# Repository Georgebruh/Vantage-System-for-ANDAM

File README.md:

# Vantage

Design files and firmware of the **Vantage** IoT sensor node, by Team sevenUP. The node is the field unit of a
flood-monitoring system. This repository holds the hardware (schematics, PCB layout, libraries, drawings and the
instruction documents) and the node firmware.

**Current release: Rev B** (2026-11-05), tag `rev-B`: power board Rev B, sensor board Rev A (unchanged).

| Board | Status |
|---|---|
| Sensor board | Schematic and PCB complete. Single-sided, made at home by toner transfer. |
| Power board | Schematic and PCB complete. One copper layer, made at home by toner transfer, same outline and mounting holes as the sensor board. |

The node is two boards joined by one 6-way JST XH cable (J1 to J1):

- **Sensor board**: carries the ESP32-S3 dev board (YD-ESP32-S3, header rows 25.4 mm apart) and the sensor
  interfaces: AJ-SR04M ultrasonic, BME280, rain gauge, TF-Luna (optional).
- **Power board**: protected 1S battery pack, solar MPPT charger module, 3.3 V LDO with ideal diode, switched
  5 V boost for the sensors (SENS_EN) and two INA226 current monitor modules.

## Repository layout

```
Vantage-Hardware/
├── sensor-board/           KiCad project of the sensor board (schematic + PCB)
├── power-board/            KiCad project of the power board (schematic + PCB)
├── lib/                    shared Vantage symbol and footprint library
├── outputs/
│   ├── sensor-board/       schematic PDF, copper artwork, assembly drawing, BOM, drill table
│   └── power-board/        schematic PDF, copper artwork, assembly drawing, envelope, BOM, drill table
├── docs/                   instruction documents (PDF)
│   └── src/                document sources, figures, fonts and build script
├── firmware/               ESP32-S3 firmware (PlatformIO) and the gateway receiver
└── tools/                  script that regenerates the drawings in outputs/
```

## Files

### KiCad design files

| File | Description |
|---|---|
| `sensor-board/Vantage_Sensor.kicad_pro` | Sensor board project (design rules for toner transfer: 0.6 / 1.0 mm tracks, 0.5 mm gaps) |
| `sensor-board/Vantage_Sensor.kicad_sch` | Sensor board schematic |
| `sensor-board/Vantage_Sensor.kicad_pcb` | Sensor board PCB, 110 × 30 mm, copper on the bottom only, two wire links on top |
| `sensor-board/fp-lib-table`, `sym-lib-table` | Project library tables, pointing to `lib/` |
| `power-board/Vantage_Power.kicad_pro` | Power board project (same design rules for toner transfer as the sensor board) |
| `power-board/Vantage_Power.kicad_sch` | Power board schematic |
| `power-board/Vantage_Power.kicad_pcb` | Power board PCB, 110 × 30 mm, copper on the bottom only, two wire links on top |
| `power-board/Vantage_Power.kicad_dru` | Custom design rule: 0.35 mm clearance between the pins of the SOT-23 parts |
| `power-board/fp-lib-table`, `sym-lib-table` | Project library tables, pointing to `lib/` |

### Library

| File | Description |
|---|---|
| `lib/Vantage.kicad_sym` | Symbols: ESP32-S3 dev board, INA226 module, CN3791 module, MAX40200, MT3608, RT9080-33, TPS2051B |
| `lib/Vantage.pretty/` | Footprints with enlarged pads for toner transfer and hand drilling; SMD footprints placed on the copper side |

### Drawings and tables (`outputs/`)

| File | Description |
|---|---|
| `outputs/sensor-board/Vantage_Sensor_Schematic.pdf` | Sensor board schematic |
| `outputs/sensor-board/Vantage_Sensor_Copper-Artwork_Letter.pdf` | Copper artwork, 1:1, four copies on US Letter. **Print at 100 % / Actual size, do not mirror.** |
| `outputs/sensor-board/Vantage_Sensor_Copper-Artwork_A4.pdf` | Same, on A4 |
| `outputs/sensor-board/Vantage_Sensor_Assembly-Drawing.pdf` | Assembly drawing, 2:1: component side and copper side |
| `outputs/sensor-board/Vantage_Sensor_BOM.csv` | Sensor board bill of materials |
| `outputs/sensor-board/Vantage_Sensor_Drill.csv` | Drill sizes and counts |
| `outputs/power-board/Vantage_Power_Schematic.pdf` | Power board schematic |
| `outputs/power-board/Vantage_Power_Copper-Artwork_Letter.pdf` | Copper artwork, 1:1, four copies on US Letter. **Print at 100 % / Actual size, do not mirror.** |
| `outputs/power-board/Vantage_Power_Copper-Artwork_A4.pdf` | Same, on A4 |
| `outputs/power-board/Vantage_Power_Assembly-Drawing.pdf` | Assembly drawing, 2:1: component side and copper side |
| `outputs/power-board/Vantage_Power_Envelope.pdf` | Module envelope, 1:1: the space the assembled board needs in the enclosure |
| `outputs/power-board/Vantage_Power_BOM.csv` | Power board bill of materials |
| `outputs/power-board/Vantage_Power_Drill.csv` | Drill sizes and counts |

### Documents (`docs/`)

The documents follow the layout of ISO documents: cover, contents, foreword, introduction, numbered clauses
(scope, references, terms, ...), normative and informative annexes, bibliography.

| File | Description |
|---|---|
| `docs/VNT-001_Sensor-board_Fabrication-assembly-test.pdf` | **VNT-001** Vantage — Sensor board — Fabrication, assembly and test |
| `docs/VNT-002_Power-board_Fabrication-assembly-test.pdf` | **VNT-002** Vantage — Power board — Fabrication, assembly and test |
| `docs/src/VNT-001.md`, `VNT-002.md` | Document sources (edit these, then rebuild the PDFs) |
| `docs/src/build.py` | Builds the PDFs from the sources |
| `docs/src/iso.css` | Page layout and styles |
| `docs/src/figures/` | Figures used by the documents |
| `docs/src/fonts/` | Caladea font (SIL Open Font License, `OFL.txt`) |

### Firmware (`firmware/`)

| File | Description |
|---|---|
| `firmware/README.md` | Setup, build environments, power modes and the data format |
| `firmware/platformio.ini` | PlatformIO project: `field` (normal operation) and `bench` (bench and functional tests) |
| `firmware/include/config.h` | Node ID, gateway URL, mounting height, intervals and battery thresholds |
| `firmware/include/pins.h` | Pin map (VNT-001, Annex C) |
| `firmware/include/secrets.example.h` | Template for the Wi-Fi credentials; copy to `secrets.h`, which is not committed |
| `firmware/src/` | Firmware sources: sensors, rain gauge, power monitors, uplink, sleep and power modes |
| `firmware/tools/receiver.py` | Receiver for the gateway computer; writes the readings to a CSV file |

### Tools

| File | Description |
|---|---|
| `tools/make_outputs.py` | Regenerates the schematic PDFs, copper artwork, assembly drawings, power board envelope and document figures with `kicad-cli`; `python3 tools/make_outputs.py power` does one board |

## Opening the design

The KiCad files are in the KiCad 7 format; KiCad 8, 9 and 10 open them. The first save in KiCad 10 upgrades the
file format; commit that upgrade on its own, without other changes, so later diffs stay readable.

Both projects use the shared library in `lib/` through their own library tables, so no global library setup is
needed.

## Title blocks

Every file carries the same title block content: **Team sevenUP**, title **Vantage — Sensor board** or
**Vantage — Power board**, date and revision. No comment lines. The documents carry the same fields in the title
block on their cover.

## Revisions

All files of a release share one revision letter, shown in every title block and on the document covers. Each
release is tagged `rev-<letter>` and listed in [`CHANGELOG.md`](CHANGELOG.md). Things that need to change are
tracked as GitHub issues.

To make a new revision:

1. Change the design in KiCad.
2. Set the new revision letter and date in the title block of every changed file (Page Settings in KiCad).
3. Regenerate the drawings: `python3 tools/make_outputs.py`, or plot them from KiCad.
4. Update the BOM and drill CSV files if parts or holes changed.
5. Update the document sources (`edition`, `date`, `rev` and the content) and rebuild: `python3 docs/src/build.py`.
6. Add the revision to `CHANGELOG.md`, commit, and tag it `rev-<letter>`.

## Rebuilding the outputs

Drawings (needs KiCad's `kicad-cli` on the PATH, or its path in `KICAD_CLI`):

```
pip install pypdf reportlab
python3 tools/make_outputs.py
```

Documents:

```
pip install markdown beautifulsoup4 weasyprint
python3 docs/src/build.py
```

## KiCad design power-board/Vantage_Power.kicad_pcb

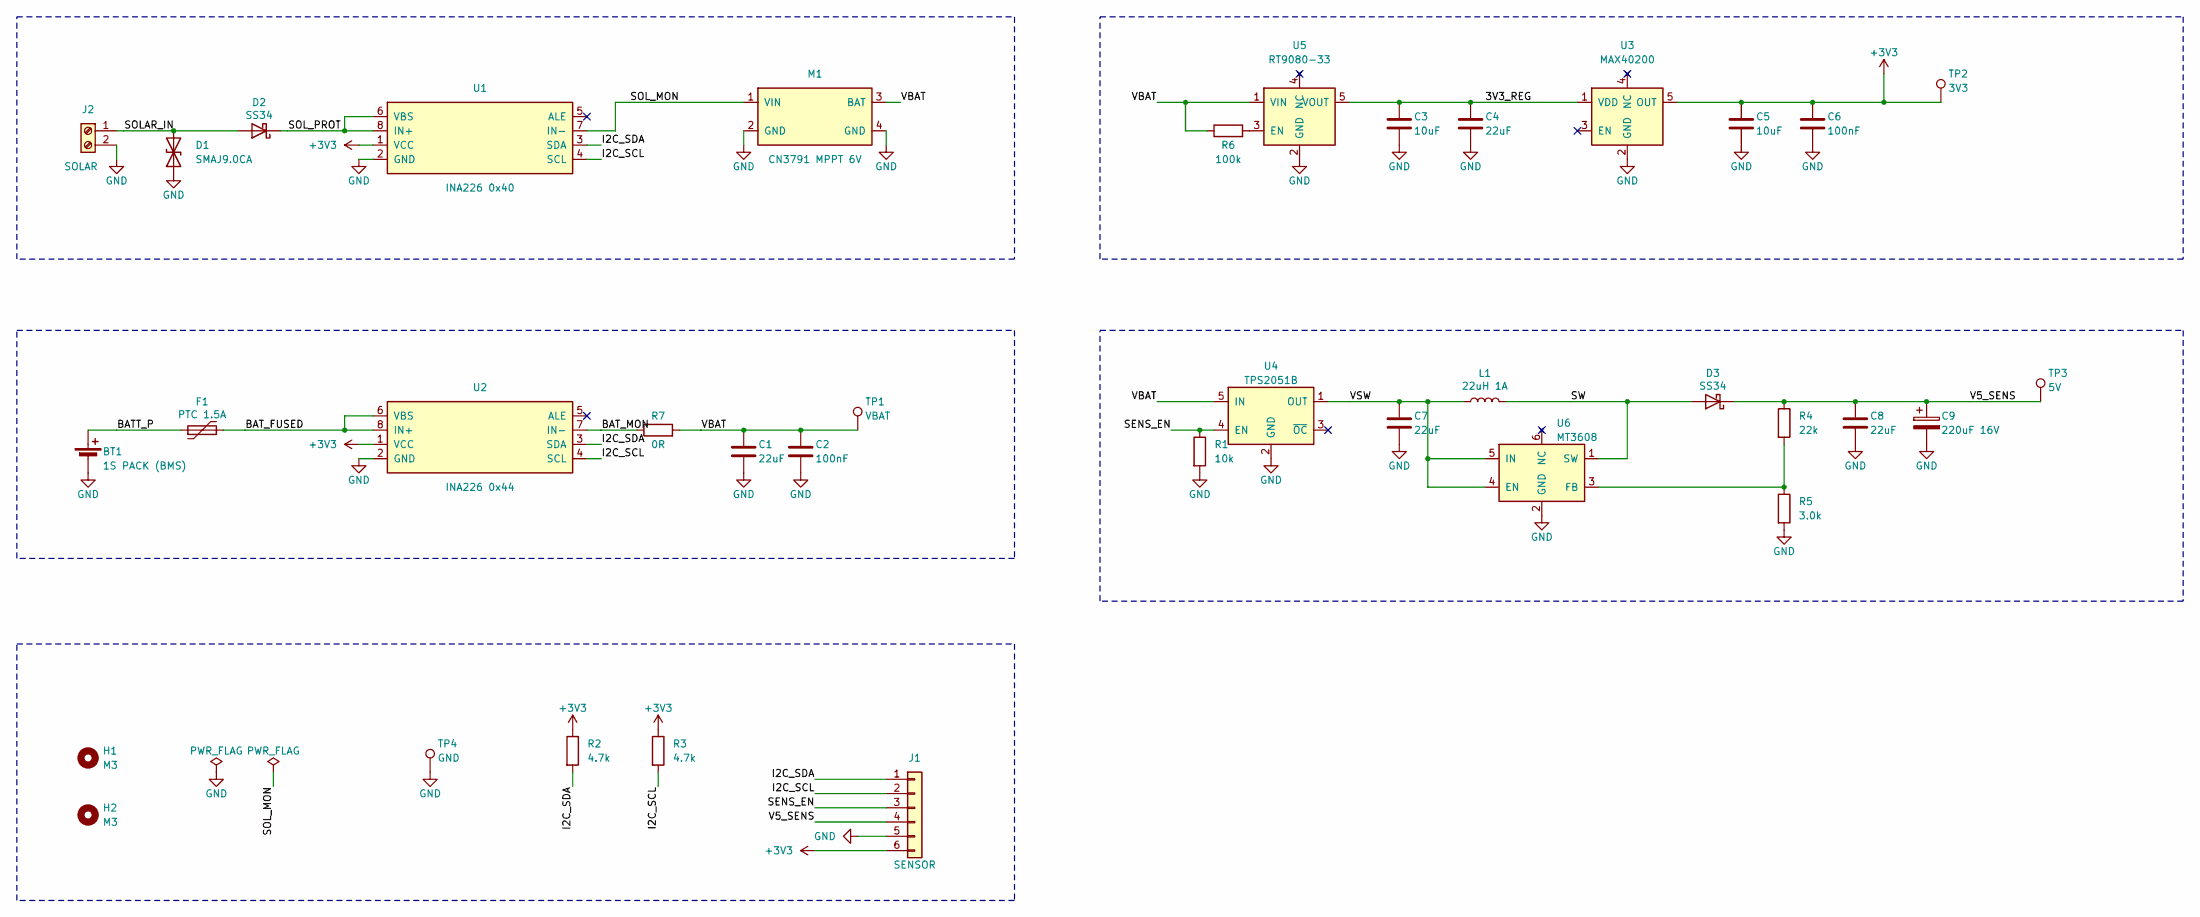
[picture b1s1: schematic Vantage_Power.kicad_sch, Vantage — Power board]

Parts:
BT1: 1S PACK (BMS); JST_XH_S2B-XH-A_1x02_P2.50mm_Horizontal_Toner
C1, C4, C7, C8: 22uF; C_1206_HandSolder_Bottom
C2, C6: 100nF; C_1206_HandSolder_Bottom
C3, C5: 10uF; C_1206_HandSolder_Bottom
C9: 220uF 16V; CP_Radial_D6.3mm_P2.50mm_Toner
D1: SMAJ9.0CA; D_SMA_HandSolder_Bottom_WideGap
D2: SS34; D_SMA_HandSolder_Bottom_WideGap
D3: SS34; D_SMA_HandSolder_Bottom
F1: PTC 1.5A; Fuse_1812_HandSolder_Bottom
H1, H2: M3; MountingHole_3.2mm_M3_KeepCopper3.5mm
J1: SENSOR; JST_XH_S6B-XH-A_1x06_P2.50mm_Horizontal_Toner
J2: SOLAR; TerminalBlock_3.5mm_1x02_Toner
L1: 22uH 1A; L_Radial_D8.0mm_P5.00mm_Toner
M1: CN3791 MPPT 6V; CN3791_Socket_1x04
R1: 10k; R_1206_HandSolder_Bottom
R2, R3: 4.7k; R_1206_HandSolder_Bottom
R4: 22k; R_1206_HandSolder_Bottom
R5: 3.0k; R_1206_HandSolder_Bottom
R6: 100k; R_1206_HandSolder_Bottom
R7: 0R; R_1206_HandSolder_Bottom
TP1: VBAT; TestPoint_Pad_D2.0mm_Bottom
TP2: 3V3; TestPoint_Pad_D2.0mm_Bottom
TP3: 5V; TestPoint_Pad_D2.0mm_Bottom
TP4: GND; TestPoint_Pad_D2.0mm_Bottom
U1: INA226 0x40; INA226_Socket_1x08_Upright
U2: INA226 0x44; INA226_Socket_1x08_Upright
U3: MAX40200; SOT-23-5_HandSolder_Bottom
U4: TPS2051B; SOT-23-5_HandSolder_Bottom
U5: RT9080-33; SOT-23-5_HandSolder_Bottom
U6: MT3608; SOT-23-6_HandSolder_Bottom

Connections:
+3V3: C5.1, C6.1, J1.6, R2.1, R3.1, TP2.1, U1.1 (VCC), U2.1 (VCC), U3.5 (OUT)
/3V3_REG: C3.1, C4.1, U3.1 (VDD), U5.5 (VOUT)
/BATT_P: BT1.1 (+), F1.1
/BAT_FUSED: F1.2, U2.6 (VBS), U2.8 (IN+)
/BAT_MON: R7.1, U2.7 (IN-)
/I2C_SCL: J1.2, R3.2, U1.4 (SCL), U2.4 (SCL)
/I2C_SDA: J1.1, R2.2, U1.3 (SDA), U2.3 (SDA)
/SENS_EN: J1.3, R1.1, U4.4 (EN)
/SOLAR_IN: D1.2 (A2), D2.2 (A), J2.1
/SOL_MON: M1.1 (VIN), U1.7 (IN-)
/SOL_PROT: D2.1 (K), U1.6 (VBS), U1.8 (IN+)
/SW: D3.2 (A), L1.2, U6.1 (SW)
/V5_SENS: C8.1, C9.1, D3.1 (K), J1.4, R4.1, TP3.1
/VBAT: C1.1, C2.1, M1.3 (BAT), R6.1, R7.2, TP1.1, U4.5 (IN), U5.1 (VIN)
/VSW: C7.1, L1.1, U4.1 (OUT), U6.4 (EN), U6.5 (IN)
GND: BT1.2 (-), C1.2, C2.2, C3.2, C4.2, C5.2, C6.2, C7.2, C8.2, C9.2, D1.1 (A1), J1.5, J2.2, M1.2 (GND), M1.4 (GND), R1.2, R5.2, TP4.1, U1.2 (GND), U2.2 (GND), U3.2 (GND), U4.2 (GND), U5.2 (GND), U6.2 (GND)
unnamed: R6.2, U5.3 (EN)
unnamed: R4.2, R5.1, U6.3 (FB)

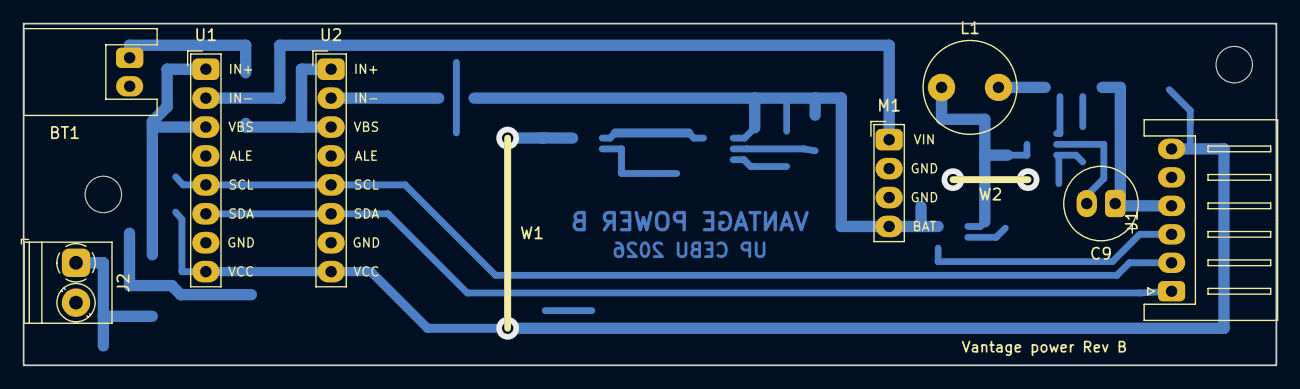
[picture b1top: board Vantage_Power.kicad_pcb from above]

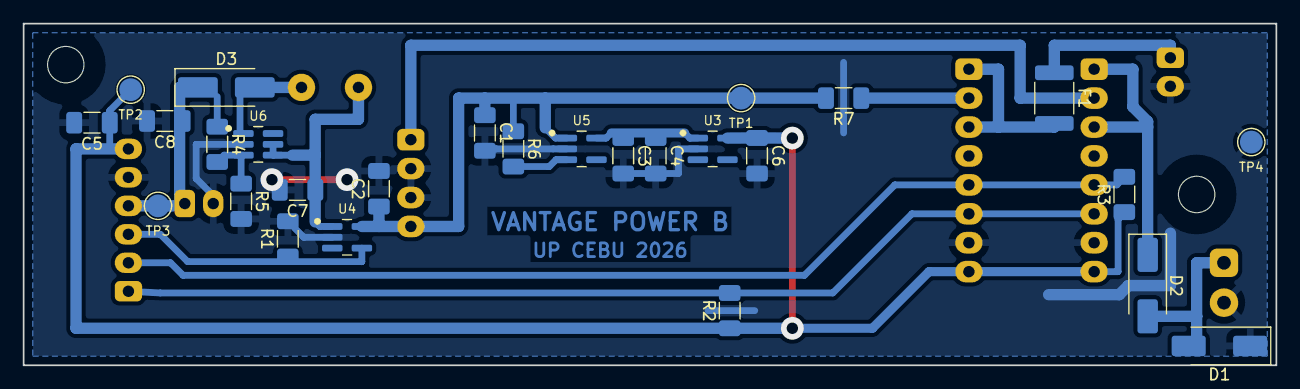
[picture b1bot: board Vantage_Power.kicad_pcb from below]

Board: 2 copper layers, 110.0 x 30.0 mm, 37 parts (27 on the bottom side), 18 nets.

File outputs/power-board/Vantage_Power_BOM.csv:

Item,Qty,References,Value,Package,Mounted on
1,1,BT1,1S PACK (BMS),"JST S2B-XH-A, XH 2-way side entry",component side
2,4,C1 C4 C7 C8,22uF,"1206 (3216), X5R/X7R, >=10 V",copper side (SMD)
3,2,C2 C6,100nF,"1206 (3216), X7R, >=10 V",copper side (SMD)
4,2,C3 C5,10uF,"1206 (3216), X5R/X7R, >=10 V",copper side (SMD)
5,1,C9,220uF 16V,"radial electrolytic 6.3 mm, 2.5 mm pitch, <=11 mm tall",component side
6,1,D1,SMAJ9.0CA,"SMA (DO-214AC), bidirectional TVS",copper side (SMD)
7,2,D2 D3,SS34,"SMA (DO-214AC), 3 A 40 V Schottky",copper side (SMD)
8,1,F1,PTC 1.5A,"1812 (4532), 1.5 A hold",copper side (SMD)
9,1,J1,SENSOR,"JST S6B-XH-A, XH 6-way side entry",component side
10,1,J2,SOLAR,"2-way screw terminal, 3.5 mm pitch",component side
11,1,L1,22uH 1A,"radial inductor 8 mm, 5 mm pitch, saturation >=1 A",component side
12,1,M1,CN3791 MPPT 6V,"1x4 female header 2.54 mm, for the CN3791 module",component side
13,1,R1,10k,1206 (3216),copper side (SMD)
14,2,R2 R3,4.7k,1206 (3216),copper side (SMD)
15,1,R4,22k,"1206 (3216), 1 %",copper side (SMD)
16,1,R5,3.0k,"1206 (3216), 1 %",copper side (SMD)
17,1,R6,100k,1206 (3216),copper side (SMD)
18,1,R7,0R,"1206 (3216), zero ohm",copper side (SMD)
19,4,TP1 TP2 TP3 TP4,VBAT 3V3 5V GND,"test pad, copper only",copper side
20,2,U1 U2,INA226 0x40 / 0x44,"1x8 female header 2.54 mm, for the INA226 modules",component side
21,1,U3,MAX40200,"SOT-23-5, MAX40200AUK",copper side (SMD)
22,1,U4,TPS2051B,"SOT-23-5, TPS2051BDBV",copper side (SMD)
23,1,U5,RT9080-33,"SOT-23-5, RT9080-33GJ5",copper side (SMD)
24,1,U6,MT3608,SOT-23-6,copper side (SMD)
